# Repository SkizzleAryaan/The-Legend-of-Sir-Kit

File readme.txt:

These examples accompany the books

  "Introduction to Embedded Systems", ISBN-13: 978-1537105727, Jonathan Valvano, copyright (c) 2021

  "Embedded Systems: Introduction to ARM Cortex M Microcontrollers",
  ISBN: 978-1469998749, Jonathan Valvano, copyright (c) 2021

  "Embedded Systems: Real Time Interfacing to Arm Cortex M Microcontrollers",
  ISBN: 978-1463590154, Jonathan Valvano, copyright (c) 2021

  "Embedded Systems: Real-Time Operating Systems for ARM Cortex M Microcontrollers",
  ISBN: 978-1466468863, Jonathan Valvano, copyright (c) 2020

Copyright 2023 by Jonathan W. Valvano, valvano@mail.utexas.edu

You may use, edit, run or distribute these file as long as the above copyright notice remains
 THIS SOFTWARE IS PROVIDED "AS IS".  NO WARRANTIES, WHETHER EXPRESS, IMPLIED
 OR STATUTORY, INCLUDING, BUT NOT LIMITED TO, IMPLIED WARRANTIES OF
 MERCHANTABILITY AND FITNESS FOR A PARTICULAR PURPOSE APPLY TO THIS SOFTWARE.
 VALVANO SHALL NOT, IN ANY CIRCUMSTANCES, BE LIABLE FOR SPECIAL, INCIDENTAL,
 OR CONSEQUENTIAL DAMAGES, FOR ANY REASON WHATSOEVER.
 For more information about my classes, my research, and my books, see
 http://users.ece.utexas.edu/~valvano/

December 29, 2022

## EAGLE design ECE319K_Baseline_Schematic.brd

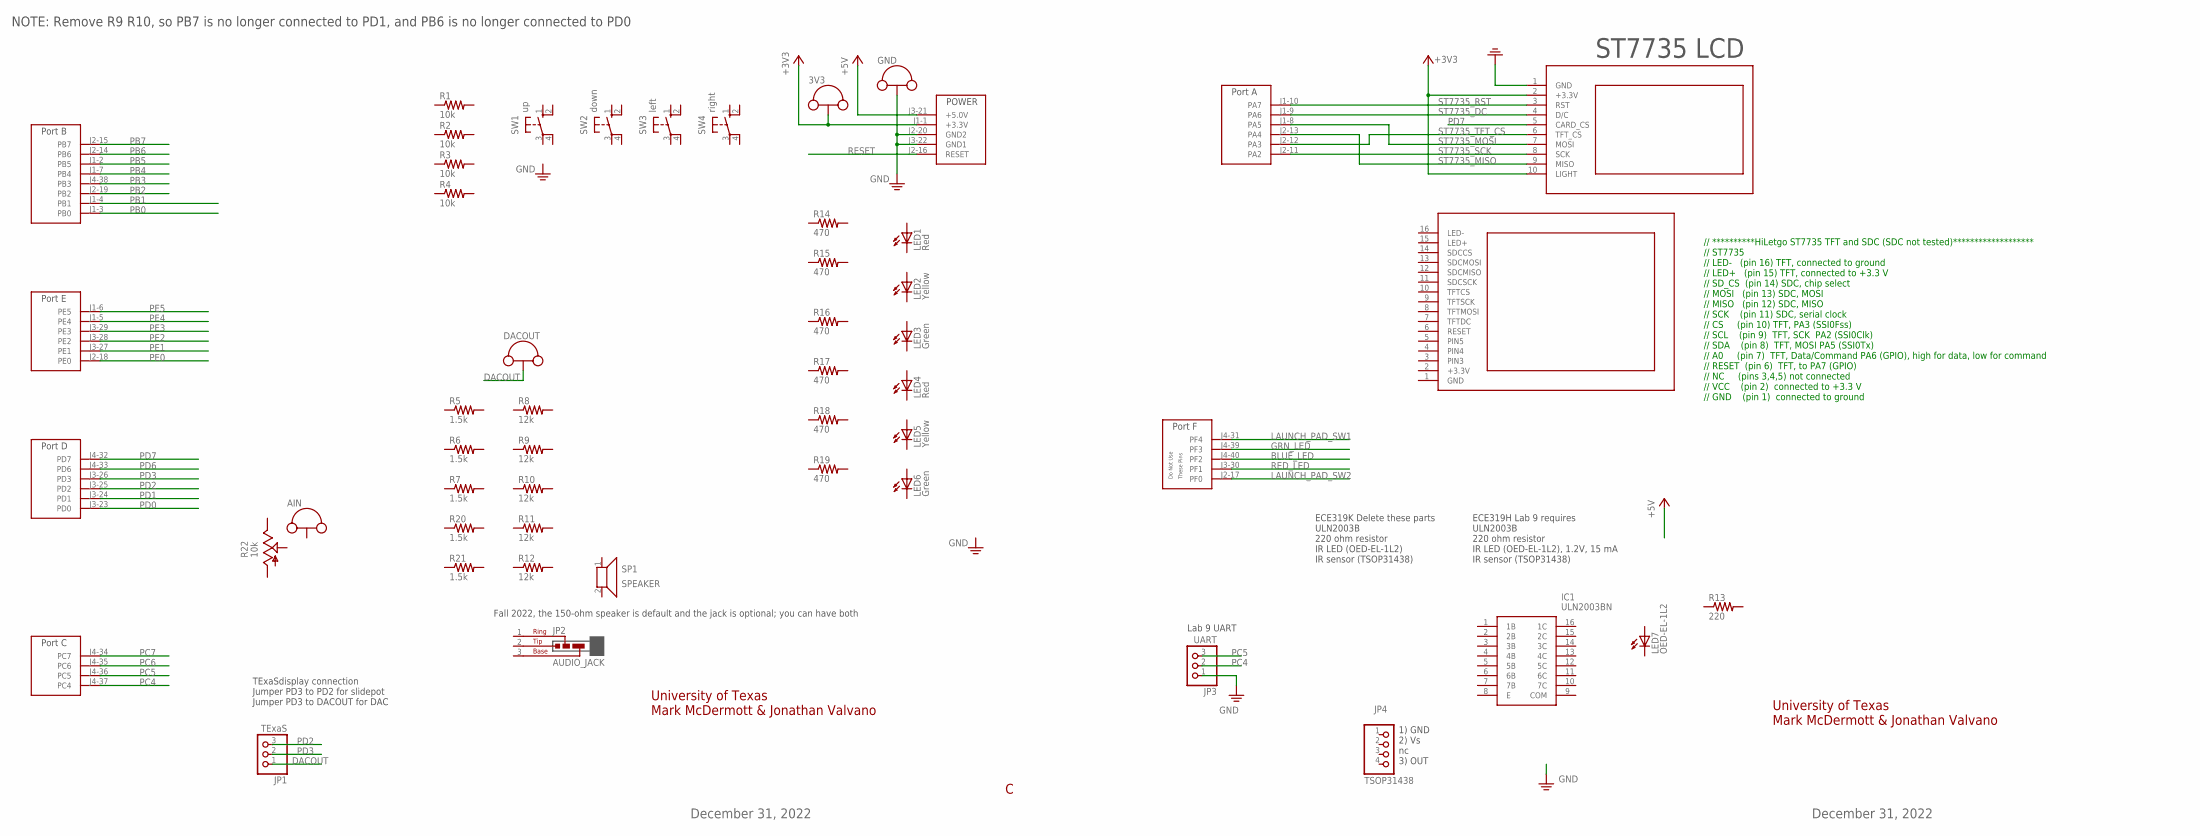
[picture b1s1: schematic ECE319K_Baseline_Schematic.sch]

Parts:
3V3: TP_LOOP
AIN: TP_LOOP
DACOUT: TP_LOOP
GND: TP_LOOP
IC1: ULN2003BN; DIP794W53P254L1930H508Q16N
JP1: TExaS; 1X03
JP2: AUDIO_JACK; JACK
JP3: UART; 1X03
JP4: TSOP31438; 1X04
LED1, LED4: Red; LED5MM
LED2, LED5: Yellow; LED5MM
LED3, LED6: Green; LED5MM
LED7: OED-EL-1L2; LED5MM
R1, R2, R3, R4: 10k; RES300MIL
R5, R6, R7, R20, R21: 1.5k; RES300MIL
R8, R9, R10, R11, R12: 12k; RES300MIL
R13: 220; RES300MIL
R14, R15, R16, R17, R18, R19: 470; RES300MIL
R22: 10k; PTA2043
SP1: SPEAKER; 1X02
SW1: up; B3F-10XX
SW2: down; B3F-10XX
SW3: left; B3F-10XX
SW4: right; B3F-10XX
U$1: HILETGO
U$2: TM4C_BP; TM4C_BOOSTER_PACK
U$3: ST7735

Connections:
+3V3: 3V3.P$1, 3V3.P$2, U$2.J1-1 (+3.3V), U$3.2 (+3.3V), U$3.10 (LIGHT)
+5V: U$2.J3-21 (+5.0V)
BLUE_LED: U$2.J4-40 (PF2)
DACOUT: DACOUT.P$1, DACOUT.P$2, JP1.1
GND: GND.P$1, GND.P$2, JP3.1, U$2.J2-20 (GND2), U$2.J3-22 (GND1), U$3.1 (GND)
GRN_LED: U$2.J4-39 (PF3)
LAUNCH_PAD_SW1: U$2.J4-31 (PF4)
LAUNCH_PAD_SW2: U$2.J2-17 (PF0)
PB0: U$2.J1-3 (PB0)
PB1: U$2.J1-4 (PB1)
PB2: U$2.J2-19 (PB2)
PB3: U$2.J4-38 (PB3)
PB4: U$2.J1-7 (PB4)
PB5: U$2.J1-2 (PB5)
PB6: U$2.J2-14 (PB6)
PB7: U$2.J2-15 (PB7)
PC4: JP3.2, U$2.J4-37 (PC4)
PC5: JP3.3, U$2.J4-36 (PC5)
PC6: U$2.J4-35 (PC6)
PC7: U$2.J4-34 (PC7)
PD0: U$2.J3-23 (PD0)
PD1: U$2.J3-24 (PD1)
PD2: JP1.3, U$2.J3-25 (PD2)
PD3: JP1.2, U$2.J3-26 (PD3)
PD6: U$2.J4-33 (PD6)
PD7: U$2.J4-32 (PD7), U$3.5 (CARD_CS)
PE0: U$2.J2-18 (PE0)
PE1: U$2.J3-27 (PE1)
PE2: U$2.J3-28 (PE2)
PE3: U$2.J3-29 (PE3)
PE4: U$2.J1-5 (PE4)
PE5: U$2.J1-6 (PE5)
RED_LED: U$2.J3-30 (PF1)
RESET: U$2.J2-16 (RESET)
ST7735_DC: U$2.J1-9 (PA6), U$3.4 (D/C)
ST7735_MISO: U$2.J2-13 (PA4), U$3.9 (MISO)
ST7735_MOSI: U$2.J1-8 (PA5), U$3.7 (MOSI)
ST7735_RST: U$2.J1-10 (PA7), U$3.3 (RST)
ST7735_SCK: U$2.J2-11 (PA2), U$3.8 (SCK)
ST7735_TFT_CS: U$2.J2-12 (PA3), U$3.6 (TFT_CS)

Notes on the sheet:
University of Texas Mark McDermott & Jonathan Valvano
December 31, 2022
ST7735 LCD
NOTE: Remove R9 R10, so PB7 is no longer connected to PD1, and PB6 is no longer connected to PD0
TExaSdisplay connection Jumper PD3 to PD2 for slidepot Jumper PD3 to DACOUT for DAC
Lab 9 UART
Fall 2022, the 150-ohm speaker is default and the jack is optional; you can have both
1) GND 2) Vs nc 3) OUT
ECE319H Lab 9 requires ULN2003B 220 ohm resistor IR LED (OED-EL-1L2), 1.2V, 15 mA IR sensor (TSOP31438)
ECE319K Delete these parts ULN2003B 220 ohm resistor IR LED (OED-EL-1L2) IR sensor (TSOP31438)
// **********HiLetgo ST7735 TFT and SDC (SDC not tested)******************* // ST7735 // LED- (pin 16) TFT, connected to ground // LED+ (pin 15) TFT, connected to +3.3 V // SD_CS (pin 14) SDC, chip select // MOSI (pin 13) SDC, MOSI // MISO (pin 12) SDC, MISO // SCK (pin 11) SDC, serial clock // CS 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

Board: 2 copper layers, 46 parts (1 on the bottom side), 14 nets, no tracks yet.

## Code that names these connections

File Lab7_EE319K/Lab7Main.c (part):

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// ST7735
// Backlight (pin 10) connected to +3.3 V
// MISO (pin 9) unconnected
// SCK (pin 8) connected to PA2 (SSI0Clk)
// MOSI (pin 7) connected to PA5 (SSI0Tx)
// TFT_CS (pin 6) connected to PA3 (SSI0Fss)
// CARD_CS (pin 5) unconnected
// Data/Command (pin 4) connected to PA6 (GPIO), high for data, low for command
// RESET (pin 3) connected to PA7 (GPIO)
// VCC (pin 2) connected to +3.3 V
// Gnd (pin 1) connected to ground

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// Silkscreen Label (SDC side up; LCD side down) - Connection
// VCC  - +3.3 V
// GND  - Ground
// !SCL - PA2 Sclk SPI clock from microcontroller to TFT or SDC
// !SDA - PA5 MOSI SPI data from microcontroller to TFT or SDC
// DC   - PA6 TFT data/command
// RES  - PA7 TFT reset
// CS   - PA3 TFT_CS, active low to enable TFT
// *CS  - (NC) SDC_CS, active low to enable SDC
// MISO - (NC) MISO SPI data from SDC to microcontroller
// SDA   (NC) I2C data for ADXL345 accelerometer
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// Silkscreen Label (SDC side up; LCD side down) - Connection
// VCC  - +3.3 V
// GND  - Ground
// !SCL - PA2 Sclk SPI clock from microcontroller to TFT or SDC
// !SDA - PA5 MOSI SPI data from microcontroller to TFT or SDC
// DC   - PA6 TFT data/command
// RES  - PA7 TFT reset
// CS   - PA3 TFT_CS, active low to enable TFT
// *CS  - (NC) SDC_CS, active low to enable SDC
// MISO - (NC) MISO SPI data from SDC to microcontroller
// X (NC) analog input X-axis from ADXL335 accelerometer
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// MOSI   (pin 13) SDC, MOSI
// MISO   (pin 12) SDC, MISO
// SCK    (pin 11) SDC, serial clock
// CS     (pin 10) TFT, PA3 (SSI0Fss)
// SCL    (pin 9)  TFT, SCK  PA2 (SSI0Clk)
// SDA    (pin 8)  TFT, MOSI PA5 (SSI0Tx)
// A0     (pin 7)  TFT, Data/Command PA6 (GPIO), high for data, low for command
// RESET  (pin 6)  TFT, to PA7 (GPIO)
// NC     (pins 3,4,5) not connected
// VCC    (pin 2)  connected to +3.3 V
// GND    (pin 1)  connected to ground
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// Tyenaza Tyenazaqhf72mi9s3
// ST7735
// LED (pin 8) connected to +3.3 V
// SCK (pin 7) connected to PA2 (SSI0Clk)
// SDA (pin 6) MOSI, connected to PA5 (SSI0Tx)
// A0  (pin 5) Data/Command connected to PA6 (GPIO), high for data, low for command
// RESET (pin 4) connected to PA7 (GPIO)
// CS  (pin 3) connected to PA3 (SSI0Fss)
// Gnd (pin 2) connected to ground
// VCC (pin 1) connected to +3.3 V

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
